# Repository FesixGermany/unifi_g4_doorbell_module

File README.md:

# Using Unifi G4 doorbell with an existing wireless bell
We had an existing wireless doorbell with a button cell powered pushbutton at our coworking-/hackerspace in use when a Unifi G4 doorbell found its way to us.
Having the ability to have multiple people being notified on their phone when someone is at the door is great combined with video and audio intercom.

We still wanted to use our existing doorbell for everyone present and who is not part of the Unifi system.

The G4 doorbell has no other output but came with a module that can be wired into the power lines claiming to be able to power a physical bell. Some tests and online search later I concluded that I do not really understand what this module exactly does and how to use its output. The only thing I know is, that the G4 shorts the power lines if someone pushes the button. If just the bell transformer is used, the voltage (18V AC) collapses, the G4 lets go of the short and everything is idle again. Using DC power seems to lead to the G4 reacting different by not letting go of the short and therefore loosing power and shutting down after a couple of seconds. If a different transformer than the one supplied or a DC power supply is used this might lead to damage or worse, so be careful and do so at your own risk!

My approach is as follows: Half wave rectify the AC voltage from the transformer so it can be switched with a power MOSFET (the G4 has its own rectifier inside so it ends up as DC anyway). In order to detect the short a microcontroller monitors the voltage, when a short is detected it disconnects power to the G4, powers up the transmitter buttom from our existing doorbell (tape used to continuously press the button and just provide power to the battery pins) and switches the power to the G4 back on. Some filtering and buffering of the power supplied to the microcontroller is neccessary as there is a disruption of power due to the short.

The finished module and the transformer were mounted on a DIN rail inside the case of an intruder alarm unitcentral unit.

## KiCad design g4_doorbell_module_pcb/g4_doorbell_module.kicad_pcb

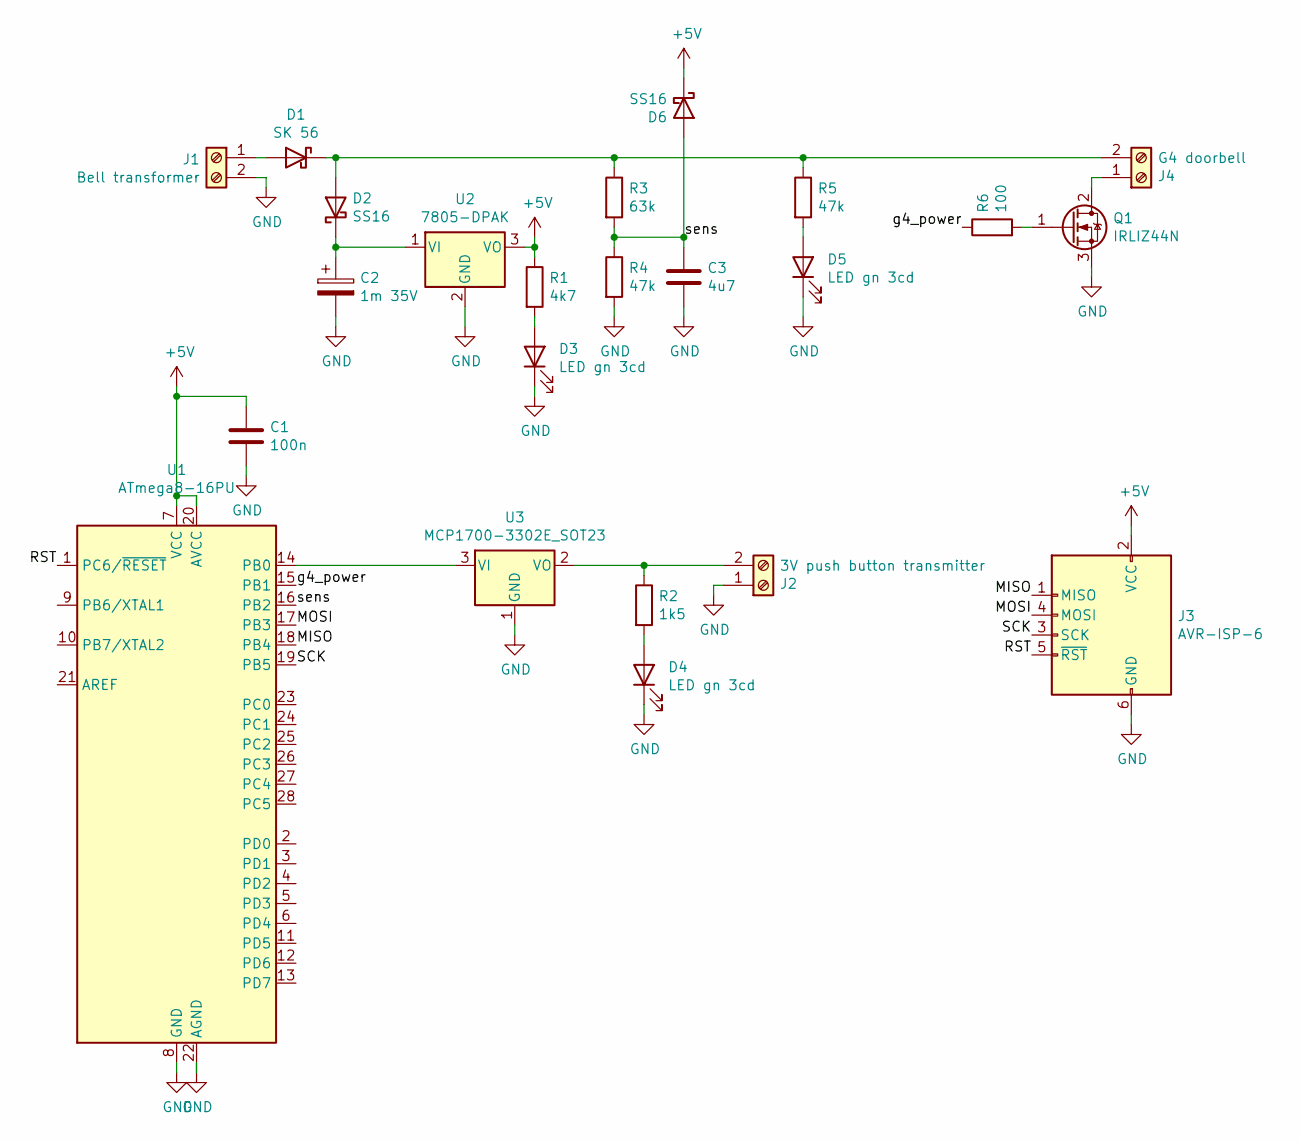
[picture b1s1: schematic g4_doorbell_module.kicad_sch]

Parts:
C1: 100n; C_0805_2012Metric_Pad1.18x1.45mm_HandSolder
C2: 1m 35V; CP_Radial_D13.0mm_P5.00mm
C3: 4u7; C_0805_2012Metric_Pad1.18x1.45mm_HandSolder
D1: SK 56; D_SMB
D2, D6: SS16; D_SMA
D3, D4, D5: LED gn 3cd; LED_D3.0mm
J1: Bell transformer; TerminalBlock_RND_205-00001_1x02_P5.00mm_Horizontal
J2: 3V push button transmitter; TerminalBlock_RND_205-00001_1x02_P5.00mm_Horizontal
J3: AVR-ISP-6; IDC-Header_2x03_P2.54mm_Vertical
J4: G4 doorbell; TerminalBlock_RND_205-00001_1x02_P5.00mm_Horizontal
Q1: IRLIZ44N; TO-220F-3_Vertical
R1: 4k7; R_0805_2012Metric_Pad1.20x1.40mm_HandSolder
R2: 1k5; R_0805_2012Metric_Pad1.20x1.40mm_HandSolder
R3: 63k; R_0805_2012Metric_Pad1.20x1.40mm_HandSolder
R4, R5: 47k; R_0805_2012Metric_Pad1.20x1.40mm_HandSolder
R6: 100; R_0805_2012Metric_Pad1.20x1.40mm_HandSolder
U1: ATmega8-16PU; DIP-28_W7.62mm
U2: 7805-DPAK; TO-252-2
U3: MCP1700-3302E_SOT23; SOT-23

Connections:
+5V: C1.1, D6.1 (K), J3.2 (VCC), R1.1, U1.7 (VCC), U1.20 (AVCC), U2.3 (VO)
/MISO: J3.1 (MISO), U1.18 (PB4)
/MOSI: J3.4 (MOSI), U1.17 (PB3)
/RST: J3.5 (~RST), U1.1 (PC6/~RESET)
/SCK: J3.3 (SCK), U1.19 (PB5)
/g4_power: R6.1, U1.15 (PB1)
/sens: C3.1, D6.2 (A), R3.2, R4.1, U1.16 (PB2)
GND: C1.2, C2.2, C3.2, D3.1 (K), D4.1 (K), D5.1 (K), J1.2, J2.1, J3.6 (GND), Q1.3 (S), R4.2, U1.8 (GND), U1.22 (AGND), U2.2 (GND), U3.1 (GND)
unnamed: D1.2 (A), J1.1
unnamed: D1.1 (K), D2.2 (A), J4.2, R3.1, R5.1
unnamed: C2.1, D2.1 (K), U2.1 (VI)
unnamed: D3.2 (A), R1.2
unnamed: D4.2 (A), R2.2
unnamed: D5.2 (A), R5.2
unnamed: J2.2, R2.1, U3.2 (VO)
unnamed: J4.1, Q1.2 (D)
unnamed: Q1.1 (G), R6.2
unnamed: U1.14 (PB0), U3.3 (VI)

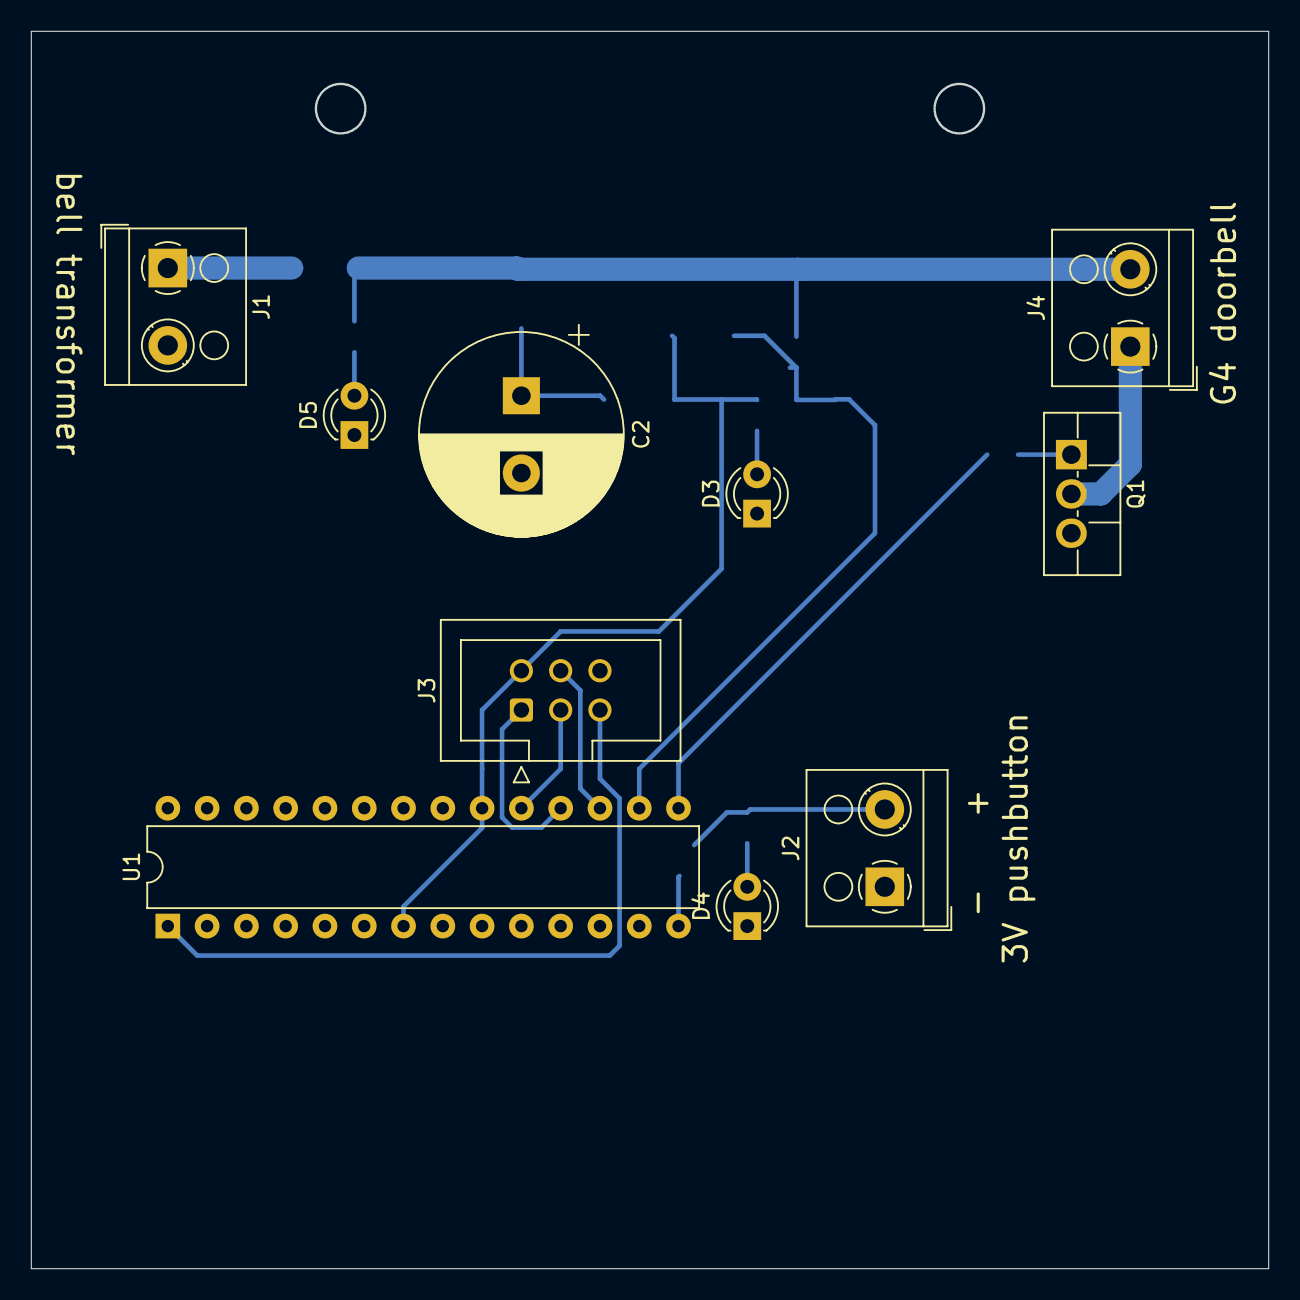
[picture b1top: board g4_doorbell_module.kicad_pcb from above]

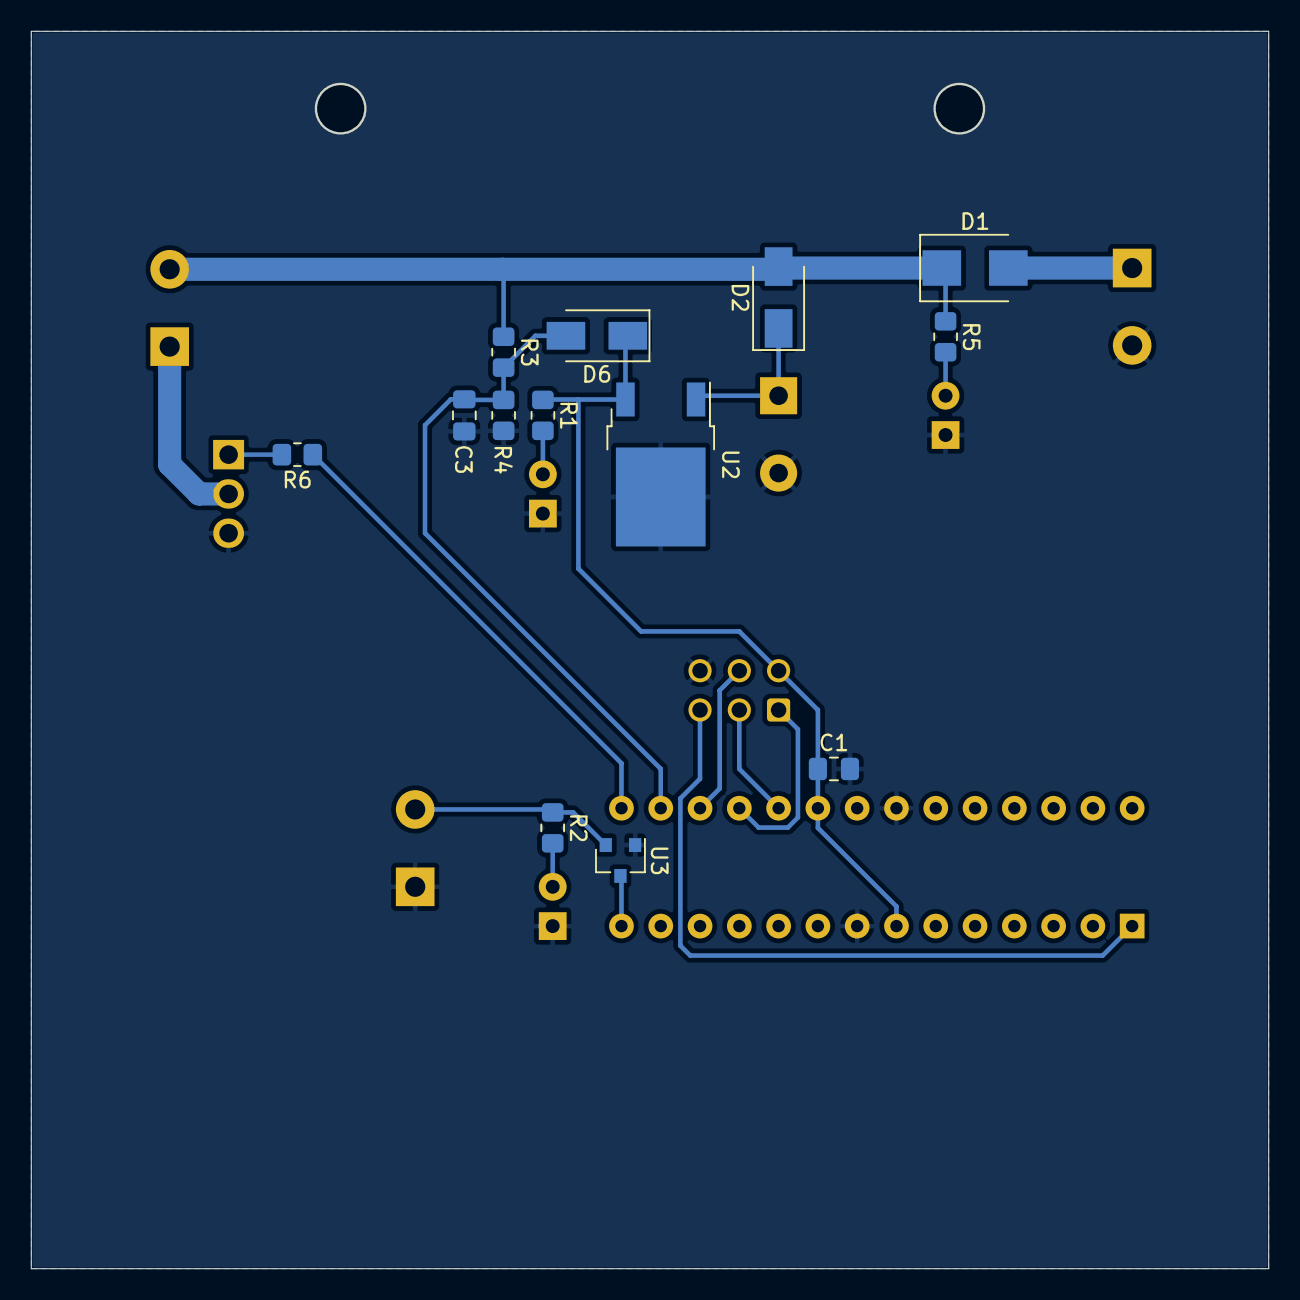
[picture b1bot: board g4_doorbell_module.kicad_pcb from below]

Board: 2 copper layers, 79.9 x 79.9 mm, 23 parts (13 on the bottom side), 18 nets.

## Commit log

2024-03-07 All finished and working
